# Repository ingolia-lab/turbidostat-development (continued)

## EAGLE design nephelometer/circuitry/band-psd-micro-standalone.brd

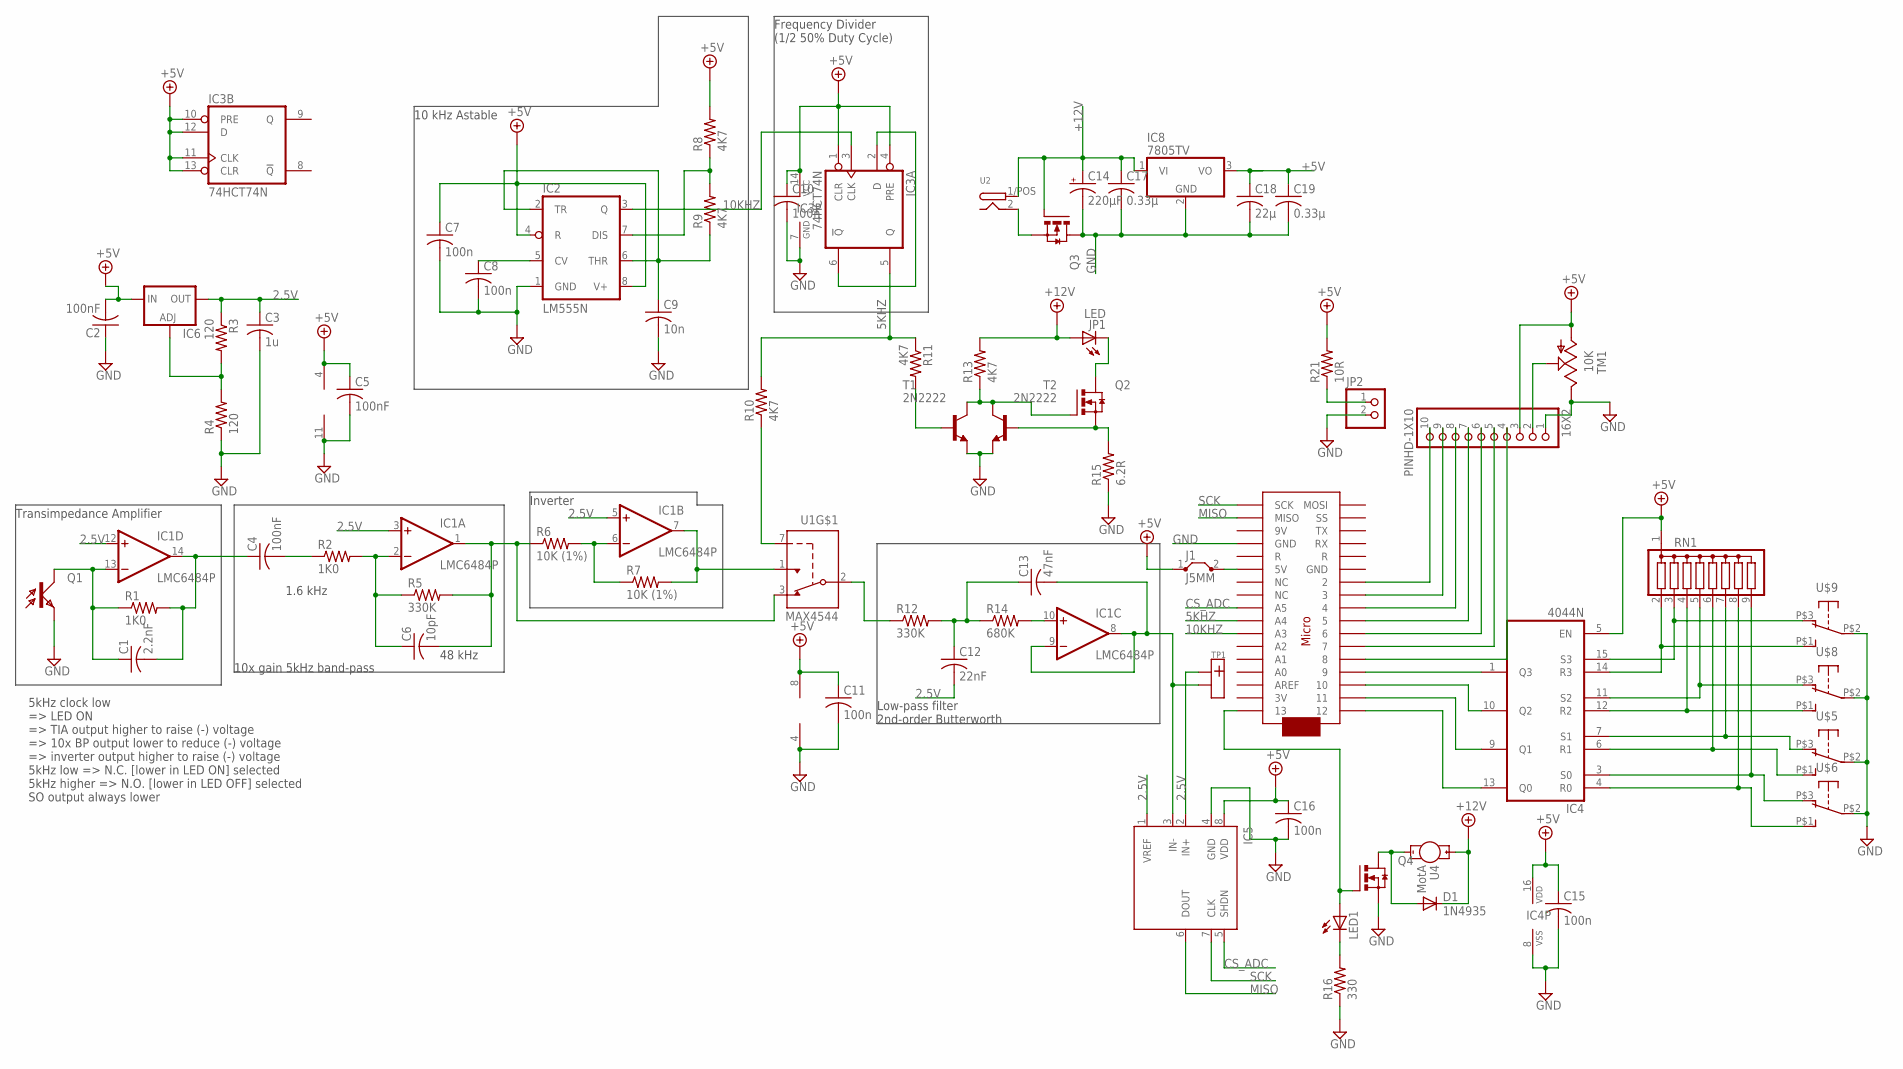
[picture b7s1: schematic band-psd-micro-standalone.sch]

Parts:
16X2: PINHD-1X10; 1X10-BIG
C1: 2.2nF; C025-024X044; DIGIKEY# BC1029CT-ND
C2, C5: 100nF; C025-025X050; DIGIKEY# BC1084CT-ND
C3: 1u; C050-024X044; DIGIKEY# 445-8614-ND
C4: 100nF; C025-060X050; DIGIKEY# 445-8325-ND
C6: 10pF; C025-024X044; DIGIKEY# BC1001CT-ND
C7, C8, C10, C11, C15, C16: 100n; C025-025X050; DIGIKEY# BC1084CT-ND
C9: 10n; C025-025X050; DIGIKEY# 445-8384-ND
C12: 22nF; C025-024X044; DIGIKEY# 445-8280-ND
C13: 47nF; C025-040X050; DIGIKEY# 445-8327-ND
C14: 220µF; E3,5-8; DIGIKEY# P5166-ND
C17, C19: 0.33µ; C025-050X050; DIGIKEY# 445-5312-ND
C18: 22µ; C050-045X075; DIGIKEY# 445-8455-ND
D1: 1N4935; DO41-10; DIGIKEY# 1N4935FSCT-ND
IC1: LMC6484P; DIL14; DIGIKEY# LMC6484AIN/NOPB-ND
IC2: LM555N; DIL08; DIGIKEY# LM555CNFS-ND
IC3: 74HCT74N; DIL14; DIGIKEY# 296-1625-5-ND
IC4: 4044N; DIL16; DIGIKEY# 296-2051-5-ND
IC5: MCP3301; DIL08; DIGIKEY# MCP3301-BI/P-ND
IC6: LM317L; 317L; DIGIKEY# 296-33312-5-ND
IC8: 7805TV; TO220V; DIGIKEY# LM7805CT-ND
J1: J5MM; 05; DIGIKEY# 0.0EBK-ND
JP1: LED; 1X02_SCREW; DIGIKEY# 475-3002-ND
JP2: PINHD-1X2; 1X02
LED1: LED3MM; DIGIKEY# 160-1139-ND
Q1: LTR-4206; 3MM_LED; DIGIKEY# 160-1030-ND
Q2, Q3, Q4: IRLB8721; TO220BV; DIGIKEY# IRLB8721PBF-ND
R1, R2: 1K0; 0204/5; DIGIKEY# S1KCACT-ND
R3, R4: 120; 0204V; DIGIKEY# S120CACT-ND
R5: 330K; 0309V; DIGIKEY# RNV14FAL330KCT-ND
R6, R7: 10K (1%); 0204/5; DIGIKEY# S10KCACT-ND
R8, R9: 4K7; 0204V; DIGIKEY# S4.7KCACT-ND
R10, R11, R13: 4K7; 0204V; DIGIKEY# S4.7KQCT-ND
R12: 330K; 0204V; DIGIKEY# RNV14FAL330KCT-ND
R14: 680K; 0204V; DIGIKEY# S680KCACT-ND
R15: 6.2R; 0204V; DIGIKEY# PPC6.2W-1CT-ND
R16: 330; 0204V; DIGIKEY# CF14JT330RCT-ND
R21: 10R; 0204V
RN1: G08R; SIL9; DIGIKEY# 4609X-101-103LF-ND
T1, T2: 2N2222; TO92-EBC-OVAL; DIGIKEY# PN2222ATFCT-ND
TM1: 10K; B25P; DIGIKEY# 3386P-103LF-ND
TP1: TEST_POINT; 1X02_SCREW
U1: MAX4544; DIL08; DIGIKEY# MAX4544CPA+-ND
U2: DC-IN-PANEL-NODETECT; 1X02_SCREW; DIGIKEY# CP-5-ND
U3: ARDUINOMICRO; DIGIKEY# 1050-1066-ND
U4: MotA; 1X02_SCREW; DIGIKEY# SC1455-ND
U$5, U$6, U$8, U$9: APE1F-5M-10-Z; APE1F-5M-10Z; DIGIKEY# 563-1183-ND

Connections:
2.5V: C3.1, C12.2, IC1.3 (+IN), IC1.5 (+IN), IC1.12 (+IN), IC5.1 (VREF), IC5.2 (IN+), IC6.2 (OUT), R3.1, TP1.1/POS (+)
5KHZ: IC3.5 (Q), R10.2, R11.1, U3.P$27 (A4)
10KHZ: IC2.3 (Q), IC3.3 (CLK), U3.P$28 (A3)
+5V: 16X2.3, C2.2, C5.1, C7.1, C10.1, C11.1, C15.1, C16.1, C18.1, C19.1, IC1.4 (V+), IC2.4 (R), IC2.8 (V+), IC3.1 (CLR), IC3.4 (PRE), IC3.10 (PRE), IC3.11 (CLK), IC3.12 (D), IC3.13 (CLR), IC3.14 (VCC), IC4.5 (EN), IC4.16 (VDD), IC5.8 (VDD), IC6.3 (IN), IC8.3 (VO), J1.1, R8.2, R21.2, RN1.1, TM1.A, U1.8 (V+)
+12V: C14.+, C17.1, D1.C, IC8.1 (VI), JP1.1/POS (A), Q3.G, R13.2, U2.1/POS (PWR), U4.1/POS (+)
CS_ADC: IC5.5 (SHDN), U3.P$26 (A5)
GND: 16X2.1, C2.1, C3.2, C5.2, C7.2, C8.2, C9.2, C10.2, C11.2, C14.-, C15.2, C16.2, C17.2, C18.2, C19.2, IC1.11 (V-), IC2.1 (GND), IC3.7 (GND), IC4.8 (VSS), IC5.4 (GND), IC8.2 (GND), JP2.2, Q1.A (E), Q3.D, Q4.S, R4.1, R15.1, R16.1, T1.E, T2.E, TM1.E, U1.4 (V-), U3.P$12 (GND), U$5.P$2 (COM), U$6.P$2 (COM), U$8.P$2 (COM), U$9.P$2 (COM)
LEDCTRL: R11.2, T1.B
MISO: IC5.6 (DOUT), U3.P$19 (MISO)
unnamed: C1.1, IC1.13 (-IN), Q1.K (C), R1.1
unnamed: C4.2, R2.1
unnamed: D1.A, Q4.D, U4.2 (-)
unnamed: IC1.6 (-IN), R6.2, R7.1
unnamed: IC1.7 (OUT), R7.2, U1.1 (NO)
unnamed: R12.1, U1.2 (COM)
unnamed: IC1.10 (+IN), R14.2
unnamed: Q2.G, R13.1, T1.C, T2.C
unnamed: C9.1, IC2.2 (TR), IC2.6 (THR), R9.1
unnamed: C8.1, IC2.5 (CV)
unnamed: IC4.9 (Q1), U3.P$2 (11)
unnamed: IC3.2 (D), IC3.6 (!Q)
unnamed: IC2.7 (DIS), R8.1, R9.2
unnamed: Q2.S, R15.2, T2.B
unnamed: IC4.13 (Q0), U3.P$1 (12)
unnamed: LED1.K (C), R16.2
unnamed: JP1.2 (K), Q2.D
unnamed: LED1.A, Q4.G, U3.P$34 (13)
unnamed: 16X2.10, U3.P$11 (2)
unnamed: JP2.1, R21.1
unnamed: C1.2, C4.1, IC1.14 (OUT), R1.2
unnamed: R10.1, U1.7 (IN)
unnamed: 16X2.9, U3.P$10 (3)
unnamed: C6.1, IC1.2 (-IN), R2.2, R5.1
unnamed: C6.2, IC1.1 (OUT), R5.2, R6.1, U1.3 (NC)
unnamed: C12.1, C13.1, R12.2, R14.1
unnamed: C13.2, IC1.8 (OUT), IC1.9 (-IN), IC5.3 (IN-), TP1.2 (-)
unnamed: 16X2.8, U3.P$9 (4)
unnamed: 16X2.7, U3.P$8 (5)
unnamed: 16X2.6, U3.P$7 (6)
unnamed: 16X2.5, U3.P$6 (7)
unnamed: IC4.15 (S3), RN1.3, U$9.P$3 (NC)
unnamed: IC4.14 (R3), RN1.2, U$9.P$1 (NO)
unnamed: IC6.1 (ADJ), R3.2, R4.2
unnamed: IC4.11 (S2), RN1.5, U$8.P$3 (NC)
unnamed: IC4.12 (R2), RN1.4, U$8.P$1 (NO)
unnamed: 16X2.2, TM1.S
unnamed: IC4.1 (Q3), U3.P$4 (9)
unnamed: IC4.6 (R1), RN1.6, U$5.P$1 (NO)
unnamed: 16X2.4, U3.P$5 (8)
unnamed: IC4.3 (S0), RN1.9, U$6.P$3 (NC)
unnamed: IC4.4 (R0), RN1.8, U$6.P$1 (NO)
unnamed: IC4.7 (S1), RN1.7, U$5.P$3 (NC)
unnamed: IC4.10 (Q2), U3.P$3 (10)
unnamed: J1.2, U3.P$23 (5V)
unnamed: Q3.S, U2.2 (GND)
SCK: IC5.7 (CLK), U3.P$18 (SCK)

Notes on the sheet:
10 kHz Astable
Frequency Divider (1/2 50% Duty Cycle)
Transimpedance Amplifier
Inverter
10x gain 5kHz band-pass
Low-pass filter 2nd-order Butterworth
5kHz clock low => LED ON => TIA output higher to raise (-) voltage => 10x BP output lower to reduce (-) voltage => inverter output higher to raise (-) voltage 5kHz low => N.C. [lower in LED ON] selected 5kHz higher => N.O. [lower in LED OFF] selected SO output always lower
48 kHz
1.6 kHz

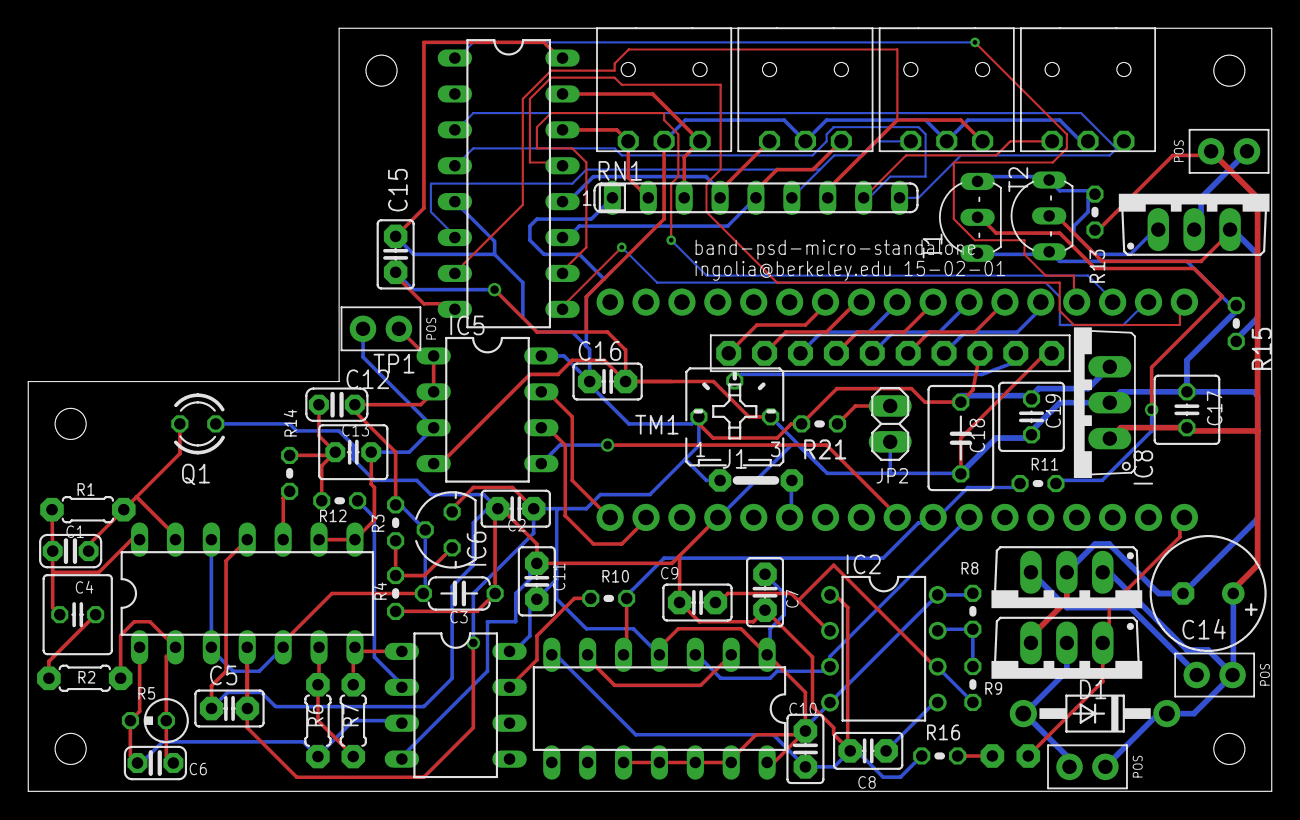
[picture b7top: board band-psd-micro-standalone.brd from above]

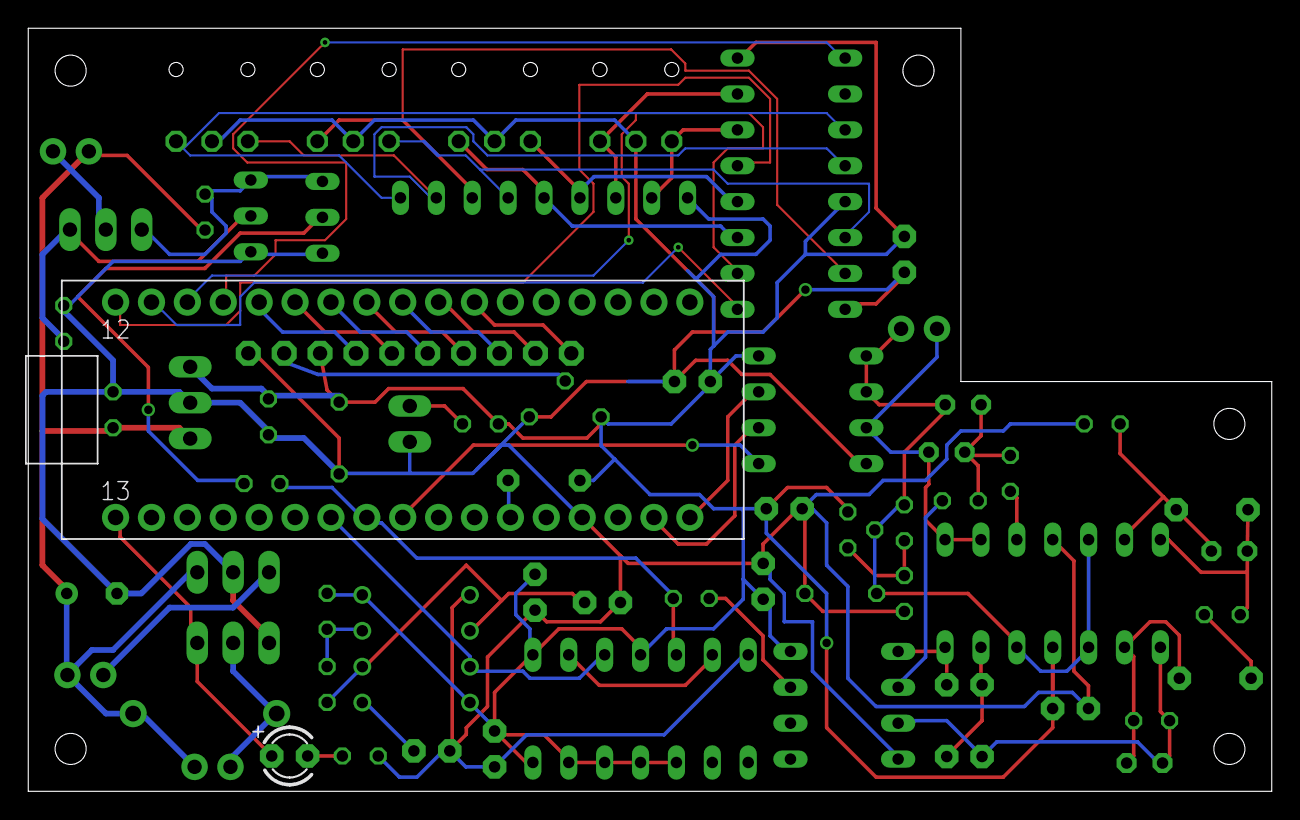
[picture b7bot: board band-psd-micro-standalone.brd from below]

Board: 2 copper layers, 88.0 x 54.0 mm, 71 parts (2 on the bottom side), 56 nets.

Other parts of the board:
U$1, U$2, U$3, U$4, U$7: M2MOUNT

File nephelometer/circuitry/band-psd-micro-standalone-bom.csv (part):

"Part";"Value";"Device";"Package";"Description";"DIGIKEY#";"DIGIKEY2#";"MANF";"MANF#";"MANF2";"MANF2#";"MF";"MPN";"OC_FARNELL";"OC_NEWARK";
"16X2";"PINHD-1X10";"PINHD-1X10";"1X10-BIG";"Pin header 1x10 0.1" spacing";"";"";"";"";"";"";"";"";"";"";
"C1";"2.2nF";"C-US025-024X044";"C025-024X044";"CAPACITOR, American symbol";"BC1029CT-ND";"";"Vishay BC Components";"K222J15C0GF5TL2";"";"";"";"";"";"";
"C2";"100nF";"C-US025-025X050";"C025-025X050";"CAPACITOR, American symbol";"BC1084CT-ND";"";"Vishay BC Components";"K104K15X7RF5TL2";"";"";"";"";"";"";
"C3";"1u";"C-US050-024X044";"C050-024X044";"CAPACITOR, American symbol";"445-8614-ND";"";"TDK Corporation";"FK28X7R1C105K";"";"";"";"";"";"";
"C4";"100nF";"C-US025-060X050";"C025-060X050";"CAPACITOR, American symbol";"445-8325-ND";"";"TDK Corporation";"FK16C0G1H104J";"";"";"";"";"";"";
"C5";"100nF";"C-US025-025X050";"C025-025X050";"CAPACITOR, American symbol";"BC1084CT-ND";"";"";"";"";"";"";"";"";"";
"C6";"10pF";"C-US025-024X044";"C025-024X044";"CAPACITOR, American symbol";"BC1001CT-ND";"";"Vishay BC Components";"K100J15C0GF5TL2";"";"";"";"";"";"";
"C7";"100n";"C-US025-025X050";"C025-025X050";"CAPACITOR, American symbol";"BC1084CT-ND";"";"";"";"";"";"";"";"";"";
"C8";"100n";"C-US025-025X050";"C025-025X050";"CAPACITOR, American symbol";"BC1084CT-ND";"";"";"";"";"";"";"";"";"";
"C9";"10n";"C-US025-025X050";"C025-025X050";"CAPACITOR, American symbol";"445-8384-ND";"";"TDK Corporation";"FK18C0G1H103J";"";"";"";"";"";"";
"C10";"100n";"C-US025-025X050";"C025-025X050";"CAPACITOR, American symbol";"BC1084CT-ND";"";"";"";"";"";"";"";"";"";
"C11";"100n";"C-US025-025X050";"C025-025X050";"CAPACITOR, American symbol";"BC1084CT-ND";"";"";"";"";"";"";"";"";"";
"C12";"22nF";"C-US025-024X044";"C025-024X044";"CAPACITOR, American symbol";"445-8280-ND";"";"TDK Corporation";"FK14C0G1H223J";"";"";"";"";"";"";
"C13";"47nF";"C-US025-040X050";"C025-040X050";"CAPACITOR, American symbol";"445-8327-ND";"";"TDK Corporation";"FK16C0G1H473J";"";"";"";"";"";"";
"C14";"220µF";"CPOL-USE3.5-8";"E3,5-8";"POLARIZED CAPACITOR, American symbol";"P5166-ND";"";"Panasonic Electronic Components";"ECA-1VM221";"";"";"";"";"";"";
"C15";"100n";"C-US025-025X050";"C025-025X050";"CAPACITOR, American symbol";"BC1084CT-ND";"";"";"";"";"";"";"";"";"";
"C16";"100n";"C-US025-025X050";"C025-025X050";"CAPACITOR, American symbol";"BC1084CT-ND";"";"";"";"";"";"";"";"";"";
"C17";"0.33µ";"C-US025-050X050";"C025-050X050";"CAPACITOR, American symbol";"445-5312-ND ";"";"TDK Corporation";"FK14X7R1H334K";"";"";"";"";"";"";
"C18";"22µ";"C-US050-045X075";"C050-045X075";"CAPACITOR, American symbol";"445-8455-ND";"";"TDK Corporation";"FK20X7R1C226M";"";"";"";"";"";"";
"C19";"0.33µ";"C-US025-050X050";"C025-050X050";"CAPACITOR, American symbol";"445-5312-ND ";"";"TDK Corporation";"FK14X7R1H334K";"";"";"";"";"";"";
"D1";"1N4935";"1N4004";"DO41-10";"DIODE";"1N4935FSCT-ND";"";"Fairchild Semiconductor";"1N4935";"";"";"";"";"";"";
"IC1";"LMC6484P";"LMC6484P";"DIL14";"SoundPLUS (TM) High Performance AUDIO OPERATIONAL AMPLIFIERS";"LMC6484AIN/NOPB-ND";"AE10012-ND";"Texas Instruments";"LMC6484AIN/NOPB";"";"";"";"";"";"";
"IC2";"LM555N";"LM555N";"DIL08";"TIMER";"LM555CNFS-ND";"AE9986-ND";"Fairchild Semiconductor";"LM555CN";"";"";"";"";"";"";
"IC3";"74HCT74N";"74HCT74N";"DIL14";"Dual D type positive edge triggered FLIP FLOP, preset and clear";"296-1625-5-ND ";"AE10012-ND";"Texas Instruments";"SN74HCT74N";"";"";"";"";"";"";
"IC4";"4044N";"4044N";"DIL16";"Quad 3-state NAND R/S LATCH";"296-2051-5-ND ";"AE9992-ND";"Texas Instruments";"CD4044BE";"";"";"";"";"";"";
"IC5";"";"MCP3301";"DIL08";"";"MCP3301-BI/P-ND";"AE9986-ND";"Microchip Technology";"MCP3301-BI/P";"";"";"";"";"";"";
"IC6";"";"LM317L";"317L";"VOLTAGE REGULATOR";"296-33312-5-ND";"";"Texas Instruments";"LM317LCLP";"";"";"";"";"";"";
"IC8";"7805TV";"7805TV";"TO220V";"Positive VOLTAGE REGULATOR";"LM7805CT-ND ";"";"Fairchild Semiconductor";"LM7805CT";"";"";"";"";"";"";
"J1";"J5MM";"J5MM";"05";"Bridge";"0.0EBK-ND";"";"Yageo";"ZOR-12-B-52-0R";"";"";"";"";"";"";
"JP1";"LED";"LED_CXN";"1X02_SCREW";"";"475-3002-ND";"492-1502-ND";"OSRAM Opto Semiconductors Inc";"SFH 4547";"Bivar Inc";"CR-174";"";"";"";"";
"JP2";"";"PINHD-1X2";"1X02";"PIN HEADER";"";"";"";"";"";"";"";"";"";"";
"LED1";"";"LED3MM";"LED3MM";"LED";"160-1139-ND";"";"Lite-On Inc";"LTL-4221N";"";"";"";"";"";"";
"Q1";"";"LTR-4206";"3MM_LED";"";"160-1030-ND";"";"Lite-On Inc";"LTR-4206E";"";"";"";"";"";"";
"Q2";"";"IRLB8721";"TO220BV";"";"IRLB8721PBF-ND";"";"";"";"";"";"";"";"";"";
"Q3";"";"IRLB8721";"TO220BV";"";"IRLB8721PBF-ND";"";"International Rectifier";"IRLB8721PBF";"";"";"";"";"";"";
"Q4";"";"IRLB8721";"TO220BV";"";"IRLB8721PBF-ND";"";"International Rectifier";"IRLB8721PBF";"";"";"";"";"";"";
"R1";"1K0";"R-US_0204/5";"0204/5";"RESISTOR, American symbol";"S1KCACT-ND ";"";"Stackpole Electronics Inc";"RNMF14FTC1K00";"";"";"";"";"";"";
"R2";"1K0";"R-US_0204/5";"0204/5";"RESISTOR, American symbol";"S1KCACT-ND ";"";"Stackpole Electronics Inc";"RNMF14FTC1K00";"";"";"";"";"";"";
"R3";"120";"R-US_0204/2V";"0204V";"RESISTOR, American symbol";"S120CACT-ND";"";"Stackpole Electronics Inc";"RNMF14FTC120R";"";"";"";"";"";"";
"R4";"120";"R-US_0204/2V";"0204V";"RESISTOR, American symbol";"S120CACT-ND";"";"Stackpole Electronics Inc";"RNMF14FTC120R";"";"";"";"";"";"";
"R5";"330K";"R-US_0309/V";"0309V";"RESISTOR, American symbol";"RNV14FAL330KCT-ND";"";"Stackpole Electronics Inc";"RNV14FAL330K";"";"";"";"";"";"";
"R6";"10K (1%)";"R-US_0204/5";"0204/5";"RESISTOR, American symbol";"S10KCACT-ND";"";"Stackpole Electronics Inc";"RNMF14FTC10K0";"";"";"";"";"";"";
"R7";"10K (1%)";"R-US_0204/5";"0204/5";"RESISTOR, American symbol";"S10KCACT-ND";"";"Stackpole Electronics Inc";"RNMF14FTC10K0";"";"";"";"";"";"";
"R8";"4K7";"R-US_0204/2V";"0204V";"RESISTOR, American symbol";"S4.7KCACT-ND ";"";"Stackpole Electronics Inc";"RNMF14FTC4K70";"";"";"";"";"";"";
"R9";"4K7";"R-US_0204/2V";"0204V";"RESISTOR, American symbol";"S4.7KCACT-ND";"";"Stackpole Electronics Inc";"RNMF14FTC4K70";"";"";"";"";"";"";
"R10";"4K7";"R-US_0204/2V";"0204V";"RESISTOR, American symbol";"S4.7KQCT-ND";"";"Stackpole Electronics Inc";"CFM14JT4K70";"";"";"";"";"";"";
"R11";"4K7";"R-US_0204/2V";"0204V";"RESISTOR, American symbol";"S4.7KQCT-ND";"";"Stackpole Electronics Inc";"CFM14JT4K70";"";"";"";"";"";"";
"R12";"330K";"R-US_0204/2V";"0204V";"RESISTOR, American symbol";"RNV14FAL330KCT-ND";"";"Stackpole Electronics Inc";"RNV14FAL330K";"";"";"";"";"";"";
"R13";"4K7";"R-US_0204/2V";"0204V";"RESISTOR, American symbol";"S4.7KQCT-ND";"";"Stackpole Electronics Inc";"CFM14JT4K70";"";"";"";"";"";"";
"R14";"680K";"R-US_0204/2V";"0204V";"RESISTOR, American symbol";"S680KCACT-ND";"";"Stackpole Electronics Inc";"RNMF14FTC680K";"";"";"";"";"";"";
"R15";"6.2R";"R-US_0204/2V";"0204V";"RESISTOR, American symbol";"PPC6.2W-1CT-ND";"";"Vishay BC Components";"PR01000106208JR500";"";"";"";"";"";"";
"R16";"330";"R-US_0204/2V";"0204V";"RESISTOR, American symbol";"CF14JT330RCT-ND ";"";"Stackpole Electronics Inc";"CF14JT330R";"";"";"";"";"";"";
"R21";"10R";"R-US_0204/2V";"0204V";"RESISTOR, American symbol";"";"";"";"";"";"";"";"";"";"";
"RN1";"";"G08R";"SIL9";"SIL RESISTOR";"4609X-101-103LF-ND";"";"Bourns Inc.";"4609X-101-103LF";"";"";"";"";"unknown";"unknown";
"T1";"2N2222";"2N2222";"TO92-EBC-OVAL";"NPN TRANSISTOR";"PN2222ATFCT-ND";"";"Fairchild Semiconductor";"PN2222ATF";"";"";"";"";"";"";
"T2";"2N2222";"2N2222";"TO92-EBC-OVAL";"NPN TRANSISTOR";"PN2222ATFCT-ND";"";"Fairchild Semiconductor";"PN2222ATF";"";"";"";"";"";"";
"TM1";"10K";"TRIM_US-B25P";"B25P";"POTENTIOMETER";"3386P-103LF-ND";"";"Bourns Inc.";"3386P-1-103LF";"";"";"";"";"";"";
"TP1";"";"TEST_POINT";"1X02_SCREW";"";"";"";"";"";"";"";"";"";"";"";
"U$5";"";"APE1F-5M-10-Z";"APE1F-5M-10Z";"";"563-1183-ND";"";"";"";"";"";"";"";"";"";
"U$6";"";"APE1F-5M-10-Z";"APE1F-5M-10Z";"";"563-1183-ND";"";"";"";"";"";"";"";"";"";
"U$8";"";"APE1F-5M-10-Z";"APE1F-5M-10Z";"";"563-1183-ND";"";"";"";"";"";"";"";"";"";
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
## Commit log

2015-01-04 Phase-sensitive detector for nepholometry
2015-01-04 Updated to use MCP3301 for ADC on stand-alone
2015-01-04 Removed tPlace annotations for push-button switch extending off of board in favor of tDocu
2015-01-04 Updated filenames for no version numbers in filename
2015-01-06 Parts list for DigiKey order
2015-01-13 SketchUp model for original band and for PSD board
2015-01-13 adjusted dimensions and orientation of bare PCB with M2 mounting dummies
2015-01-15 Finished enclosing tall part of the board
2015-01-15 Finished covering component side of casing
2015-01-15 Finished basic enclosure for component side and all around
2015-01-15 Tabs for mounting a back cover
2015-01-16 Fixed 10.5 spacing between pushbutton switches
    Added holes for 3.5mm jack for motor, DC IN, and pushbuttons
2015-01-19 Fixed a minor flaw in which Arduino input pin is connected on the wrong side of the base resistor of the LED control and so never reads positive
2015-01-19 Test control firmware for Micro to read SPI from analog-digital converter and record state of oscillators while switching the motor on and off
2015-01-19 Housing for standalone board with Arduino Micro next to 500 ml band
2015-01-27 Enlarged board, included 5V regulator on board, more decoupling, 4 buttons on 4 PCIO pins
2015-01-28 Fixed up filter design -- topology of high-gain bandpass and component values for low-pass
2015-01-28 Better wiring for push-buttons (to PCINT pins) and LCD (allow INT)
2015-01-29 Started routing power supply
    Started part numbers for filter components
2015-01-31 Specific parts for all analog components
2015-02-01 Routed most of board except push-buttons and latch
2015-02-02 Finished routing traces, all DRC okay
2015-02-02 Finished placement labels and added test point
2015-02-02 Finished BOM part assignments
2015-02-02 Finished BOM attributes needed for 15-02-01 test fabrication
2015-02-03 Automatically parse BOM table
2015-02-03 Finished script to extract a Digi-Key BOM and a parts list for assembly
2015-02-03 Parts list and assembly for 15-02-01 PCB
2015-02-03 Remove old .numbers BOM
2015-02-03 Fixup extraneous space in part #
2015-02-14 Spice model of the phase-sensitive detector circuit
2015-06-11 New "DSP" amplifier i.e. control LED from microcontroller and no invert / switch / average in hardware
2015-06-13 Finalized minimal turbidostat circuit with Arduino Micro control
2015-06-24 Model of DSP micro board and start on housing with screw "platforms"
2015-06-24 Housing for PCB including screw recesses
2015-06-26 Created one-piece housing with separate back, and mounting points for motor clip
2015-06-26 Separated PCB housing and bottle band into two units with a square protrusion from the PCB housing into the band Reorient prints for minimal support wiht no supports in the "middle" of the housing
2015-07-04 Firmware implementing turbidity measurements with DSP averaging including per-point tests and overall sampling
2015-07-09 Thickened all walls of the housing
2015-07-09 Fixed up interface between band and the main housing body
2015-07-09 Laid out new housing for printing, in 3 pieces
2015-07-10 Changed out screw holes for 2mm diameter mounting pegs
2015-07-12 Ignore backup files
2015-07-12 Ordering plans for first round of stand-alone Arduino Micro doing DSP PSD
2015-07-13 Updated parts list based on first round of building turbidostats
2015-07-13 New measurement sequence
2015-07-13 Merged old turbidostat controller code
2015-10-13 Report turbido time from start; version stamp
2016-10-10 Moved hole for 1/8 in jack for motor connection
2016-10-22 Right part number for dual op amp and socket
2016-11-12 Teensy-based nephelometer board using on-board ADC
2016-11-12 programmable gain amplifier incorporated
2016-11-14 Stackable motor controller board w/ 3.3V control; USB versus wall power; test order for components
2016-11-26 Laid out circuit for teensy nephelometer
2016-11-27 Designed motor power board to stack on nephelometer or run over RJ11 cable
2016-11-29 Motor control with transistor gating MOSFET, shutoff when disconnected
2016-11-29 Simulation of motor control circuit
2016-12-16 Corrected resistor divider
2016-12-19 Teensy firmware to strobe LED and control SPI PGA
2017-01-11 Revised detector board circuit, picked filter values, finalized parts
2017-01-18 Finalized parts and components for 10kHz band-pass etc
2017-01-18 Fixed really dumb lack of trace to a test pin
2017-02-10 Frequency & ADC tuning; measurement; simple event loop
2017-02-10 Useful data sheets
2017-02-11 Separate 3V3 supply for analog circuits. Guard ring for TIA
2017-02-11 Added manual pumping with choice of motor
2017-02-21 Adjust the PGA gain
2017-02-21 Refactored nephelometer out from event loop
2017-02-22 Refactoring nephelometer into c++
2017-02-22 Clean build
2017-02-22 Started C++ abstracted turbidostat class
2017-02-22 Abstraction for a Pump
2017-02-22 Work to implement the turbidostat
2017-02-22 Base class for all growth controllers
2017-02-22 Refactoring for a global supervisor
2017-02-23 Major refactor for parameter super-class including nephel settings; built manual command functions; pulled loop into supervisor
2017-02-23 Infrastructure for starting and looping controllers
2017-02-23 Infrastructure for configuring controllers
2017-02-23 Handle error beginning controller
2017-02-24 Refactoring to make manual mode a controller, avoid all pointers
2017-02-25 Working supervisor event loop, minor UI improvements
2017-02-25 Minor UI improvements
2017-02-25 Error settign up nephelometer
2017-02-25 Implemented trophostat; improved some abstractions; started test rig nepheloometer
2017-02-25 Finished test stub nephelometer
2017-02-25 Improved test nephelometer stub; better abstractions for turbidostat
2017-02-25 Test nephelometer stub accounts for good & bad media
2017-02-26 Cleaner interface for Tropho controller and good setup to test it
2017-02-26 Random noise to measurements
2017-02-27 Switched trophostat to target a fuzzy range
2017-02-27 New turbidostatic controller with a tuned periodic mix from two pumps
2017-03-03 Set up pins early and dont use pinMode after SPI.begin
2017-03-20 Added # signs and changed printouts in places. Added pump stop commands to the end of every controller program. Expanded the useTestNephel() function to allow escape from it. All changes are initiale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
2017-03-27 Added changes that allow for a stepping mode. It provides 5 pre-defined steps at a pre-defined time interval. Small syntax changes in supervisor.ino for printed items.
2017-04-04 Created a StepTurbido child class. Having problems with the constructor, doesn't compile.
2017-04-05 Fixed the stepping turbidostat class. Started writing the stepping turbidostat mix class. Currently does not compile.
2017-04-05 Created the StepTurbidoMix child class. minor updates to stepTurbido class. Added lots of comments to both of theseclasses.
2017-04-05 Added extra algorithm and clarification to StepTurbidoMix class.
2017-04-07 Logic fixed in the Step* child classes. Should be functional now. Commenting added. Rearranged functions to make more sense.
2017-04-07 copy/paste error
2017-04-07 Added double-loop to StepTurbidoMix, similar to StepTurbido, so that time counts correctly on the final step.
2017-04-08 Fixed setting the bounds in StepTurbido. Logic was off by ten.
2017-06-03 Feather-based board with external ADC
2017-06-05 Feather motor controller board with ESD protection and up to 4 motors or 2 motors plus stepper
2017-06-07 Finalized Feather nephelometer with separate ADC and 4 robust motor controls
2017-06-19 Firmware for new Feather based boards
2017-06-20 Update for feather boards -- pins, no EEPROM params, cleaner parameter setting
2017-06-21 refactoring for derived turbidostats
2017-06-21 Refactor for better derivation of mixed-media turbidostat. Cleaned up warnings
2017-06-21 More scheduled turbidostat cycles
2017-06-21 syringe pump driver
2017-06-22 Minor bug fixes from testing
2017-06-30 Minor updates after test assembly
2017-08-17 Nephelometer PGA setting through settings interface
2017-08-17 Documentation
2017-08-17 Hierarchy of turbidostat variants including multi-pump algorithms
2017-08-17 Aggregate measurements over a window and vote for too low / too high
2017-09-28 Keep turbidostat off at first
2017-09-28 reorganized old versions
2017-09-29 Reorganization and moving data sheets out of VC
2017-09-29 Rearranging and adding part ordering information
2017-09-29 More rearrangement especially ordering information
2017-09-29 Exported native and STL format from Fusion
2017-09-29 Cleaned up firmware
2017-12-06 Switch media automatically
2017-12-30 Added initialization time to the concentration log-gradient controller
2018-01-04 Moved delay to the end of the base loop
2018-01-04 Add virtual override for turbidity-controlled pumping
2018-01-04 Periodic pulse controller
2018-01-04 Make pulse controller available
2018-01-08 Controller implementing density gradients. Fixed reading of negative fixed-point numbers
2018-01-10 Virtualize measurement settings -- make overrideable
2018-03-13 Pullup resistor to shut off motors during startup with high-Z pin on microcontroller. Replaced obsolete flyback diode.
2018-06-17 Started documentation of turbidostat
2018-06-17 Instructions are markdown
2018-06-25 Library components for blue light box
2018-06-25 Fix display of negative measurements; single target neph for tstat; log target neph for tstat
2018-06-25 Use long denoms for quot/rem
2018-06-25 Inherit display for turbidostat
2018-06-25 Correct display of negative numbers from manual measurement
2018-06-25 Always start the configured controller
2018-06-25 Fix bug in requiring non-negative neph target
2018-06-25 Fix inherited controller displays and other cosmetics
2018-06-25 Better names for controllers
2018-07-09 Assembling the electronics
2018-07-09 Minor clarifications to operating instructions
2018-07-10 Minor clarifications
2018-07-14 Libraries and some raw images
2018-07-14 Illustrated LED assembly
2018-07-14 Fixed image placement
2018-07-14 Added stray picture
2018-07-14 Illustrated Feather header assembly
2018-07-14 Fixed small errors
2018-07-14 Organized images into subdirectory
2018-07-14 Started sub-dividing construction information
2018-07-14 Notes on wiring the pump input
2018-07-14 Fixed link syntax
2018-07-14 Split off housing assembly into a separate file
2018-07-14 Split off fluidics and pump
2018-07-14 Instructions for mounting and wiring the pump
2018-07-14 Fixed filenames
2018-07-14 Picture of assembled system
2018-07-14 Started writing instructions for turbidostat growth
2018-07-15 Pictures of housing assembly
2018-07-15 Wrote instructions for assembling housing
2018-07-15 Edits to housing assembly instructions
2018-07-15 Example text for testing Feather
2018-07-15 Added example output for inoculation and turbidostat
2018-07-15 Split apart operation instructions
2018-07-15 Overview of docs
2018-07-20 Corrected syringe filter description
2018-07-20 Corrected formatting of sub-list
2018-07-20 Split apart turbidostat output
2018-07-20 Fixed indentation of output
2018-07-29 Fixed file path
2018-07-29 Part number for JST cable
2018-07-29 Part number for stirring
